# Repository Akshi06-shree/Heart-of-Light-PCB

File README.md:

# Heart-of-Light-PCB
My first electronics project – from hand-drawn circuit to fabricated PCB using KiCad.

# ❤️ Heart Of Light – My First PCB Project

My first electronics project, where I converted a hand-drawn circuit into a working, fabricated PCB.

## 🛠️ Components Used
- LEDs
- 220 Ω and 10 kΩ resistors
- NE555 Timer IC
- 10 µF capacitor
- CR2450 battery
- SPDT slide switch

  ## 📍 NE555 Timer IC – Pin Configuration

**IC:** LM555xN (DIP-8)

| Pin No. | Pin Name | Connection in My Circuit |
|---|---|---|
| 1 | GND | Connected to Ground (Battery −) |
| 2 | TRIG | Connected to timing capacitor junction |
| 3 | OUT | Connected to the LED and resistor network |
| 4 | RESET | Connected to +3V supply |
| 5 | CONT | Not connected |
| 6 | THRES | Connected to timing capacitor junction |
| 7 | DISCH | Connected to the junction of R17 and R18 |
| 8 | VCC | Connected to +3V supply |

### ⏱️ Timing Circuit Connections
- R17 – 10 kΩ
- R18 – 10 kΩ
- C1 – 100 µF
- Pin 2 and Pin 6 share the timing junction.
- Pin 7 connects between R17 and R18.

## 💻 Tools Used
- Tinkercad – Circuit simulation
- KiCad – Schematic and PCB design
- JLCPCB Viewer – Gerber and DFM review
- LionCircuits – PCB fabrication

## 🔄 Project Workflow
1. Hand-drawn circuit
2. Tinkercad simulation
3. Breadboard testing
4. KiCad schematic design
5. PCB layout and 3D view
6. Gerber generation and review
7. PCB fabrication and testing

## 🎯 Outcome
Successfully designed, fabricated and tested my first heart-shaped PCB.

This project helped me gain practical knowledge of electronic circuits and PCB design.

## 👩‍💻 Author
**Akshidha Shree G.R.**  
Biomedical Engineering Student

*Small project, big learning experience! ❤️*

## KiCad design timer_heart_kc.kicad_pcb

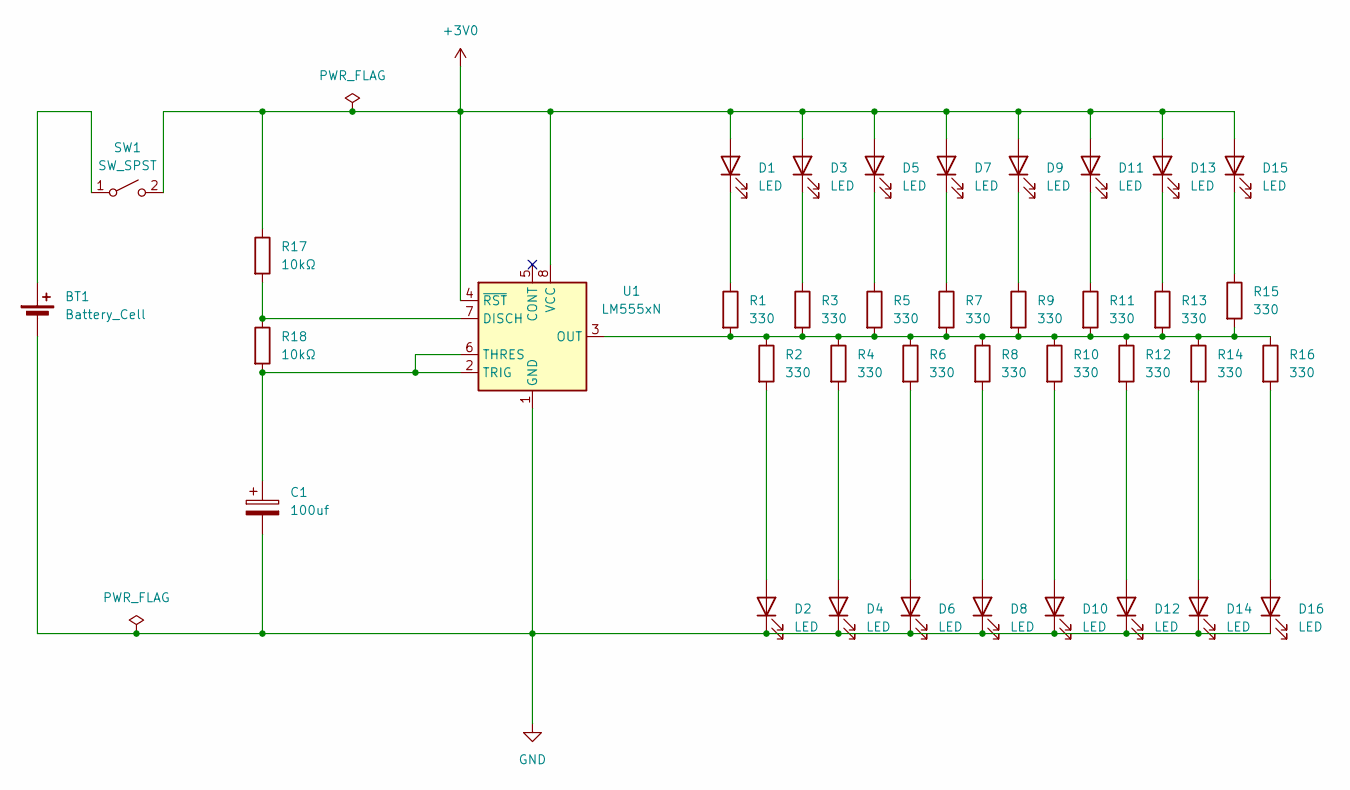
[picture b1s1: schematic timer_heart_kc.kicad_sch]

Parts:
BT1: Battery_Cell; BatteryHolder_Keystone_106_1x20mm
C1: 100uf; CP_Radial_D5.0mm_P2.00mm
D1, D2, D3, D4, D5, D6, D7, D8, D9, D10, D11, D12, D13, D14, D15, D16: LED; LED_D3.0mm
R1, R2, R3, R4, R5, R6, R7, R8, R9, R10, R11, R12, R13, R14, R15, R16: 330; R_Axial_DIN0207_L6.3mm_D2.5mm_P7.62mm_Horizontal
R17, R18: 10kΩ; R_Axial_DIN0207_L6.3mm_D2.5mm_P7.62mm_Horizontal
SW1: SW_SPST; SW_Slide_SPDT_Straight_CK_OS102011MS2Q
U1: LM555xN; DIP-8_W7.62mm

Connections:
+3V0: D1.2 (A), D3.2 (A), D5.2 (A), D7.2 (A), D9.2 (A), D11.2 (A), D13.2 (A), D15.2 (A), R17.1, SW1.2 (B), U1.4 (~RST), U1.8 (VCC)
GND: BT1.2 (-), C1.2, D2.1 (K), D4.1 (K), D6.1 (K), D8.1 (K), D10.1 (K), D12.1 (K), D14.1 (K), D16.1 (K), U1.1 (GND)
unnamed: BT1.1 (+), SW1.1 (A)
unnamed: D1.1 (K), R1.1
unnamed: D2.2 (A), R2.2
unnamed: D3.1 (K), R3.1
unnamed: D4.2 (A), R4.2
unnamed: D5.1 (K), R5.1
unnamed: D6.2 (A), R6.2
unnamed: D7.1 (K), R7.1
unnamed: D8.2 (A), R8.2
unnamed: D9.1 (K), R9.1
unnamed: D10.2 (A), R10.2
unnamed: D11.1 (K), R11.1
unnamed: D12.2 (A), R12.2
unnamed: D13.1 (K), R13.1
unnamed: D14.2 (A), R14.2
unnamed: D15.1 (K), R15.1
unnamed: D16.2 (A), R16.2
unnamed: R17.2, R18.1, U1.7 (DISCH)
unnamed: R1.2, R2.1, R3.2, R4.1, R5.2, R6.1, R7.2, R8.1, R9.2, R10.1, R11.2, R12.1, R13.2, R14.1, R15.2, R16.1, U1.3 (OUT)
unnamed: C1.1, R18.2, U1.2 (TRIG), U1.6 (THRES)

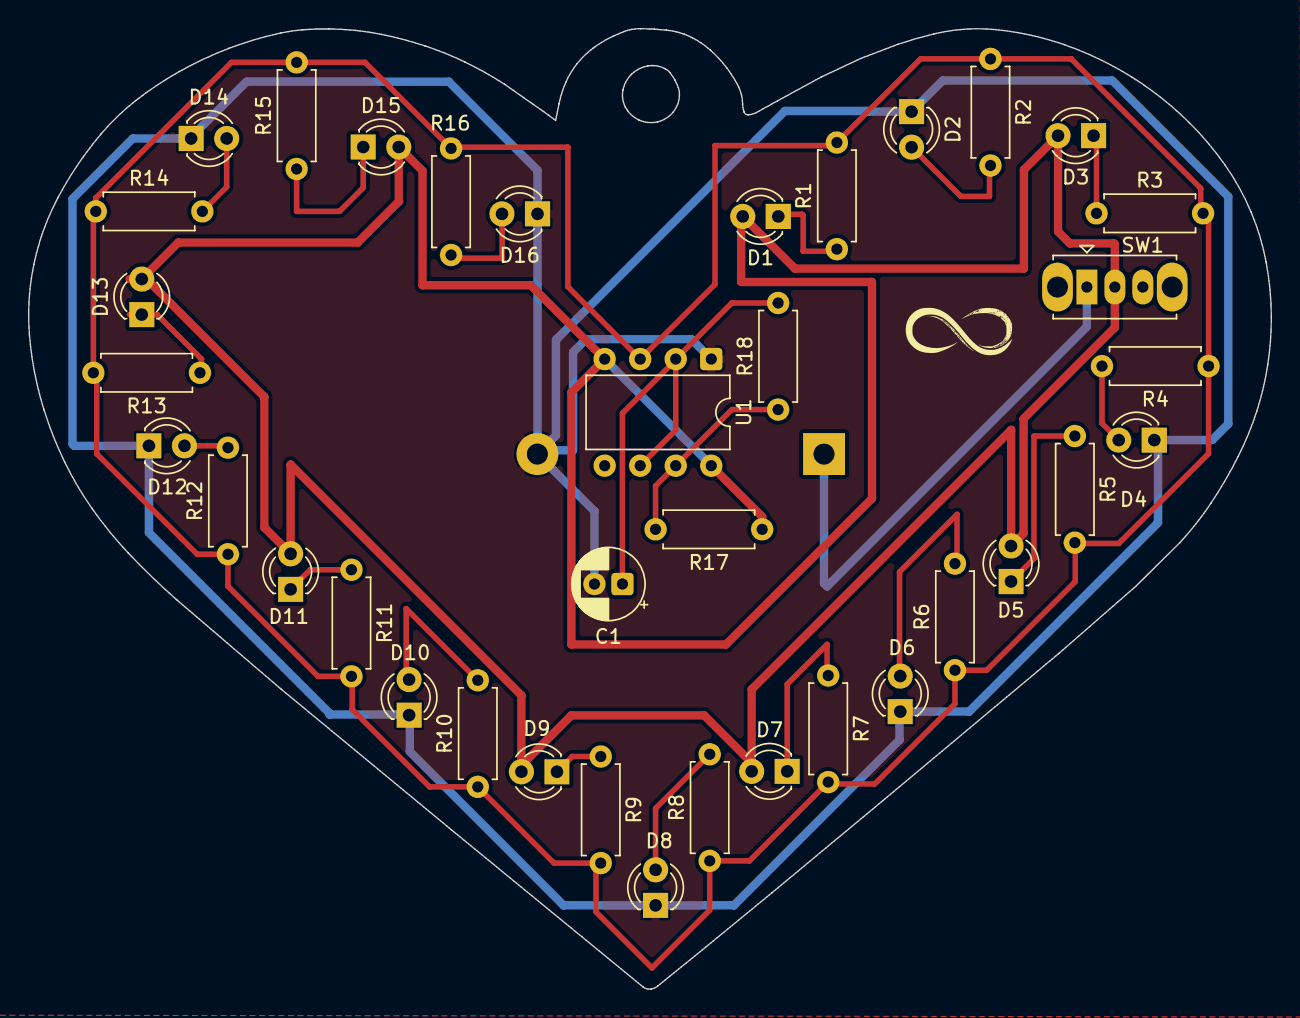
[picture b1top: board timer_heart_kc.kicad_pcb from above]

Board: 2 copper layers, 88.8 x 68.7 mm, 38 parts (1 on the bottom side), 22 nets.
